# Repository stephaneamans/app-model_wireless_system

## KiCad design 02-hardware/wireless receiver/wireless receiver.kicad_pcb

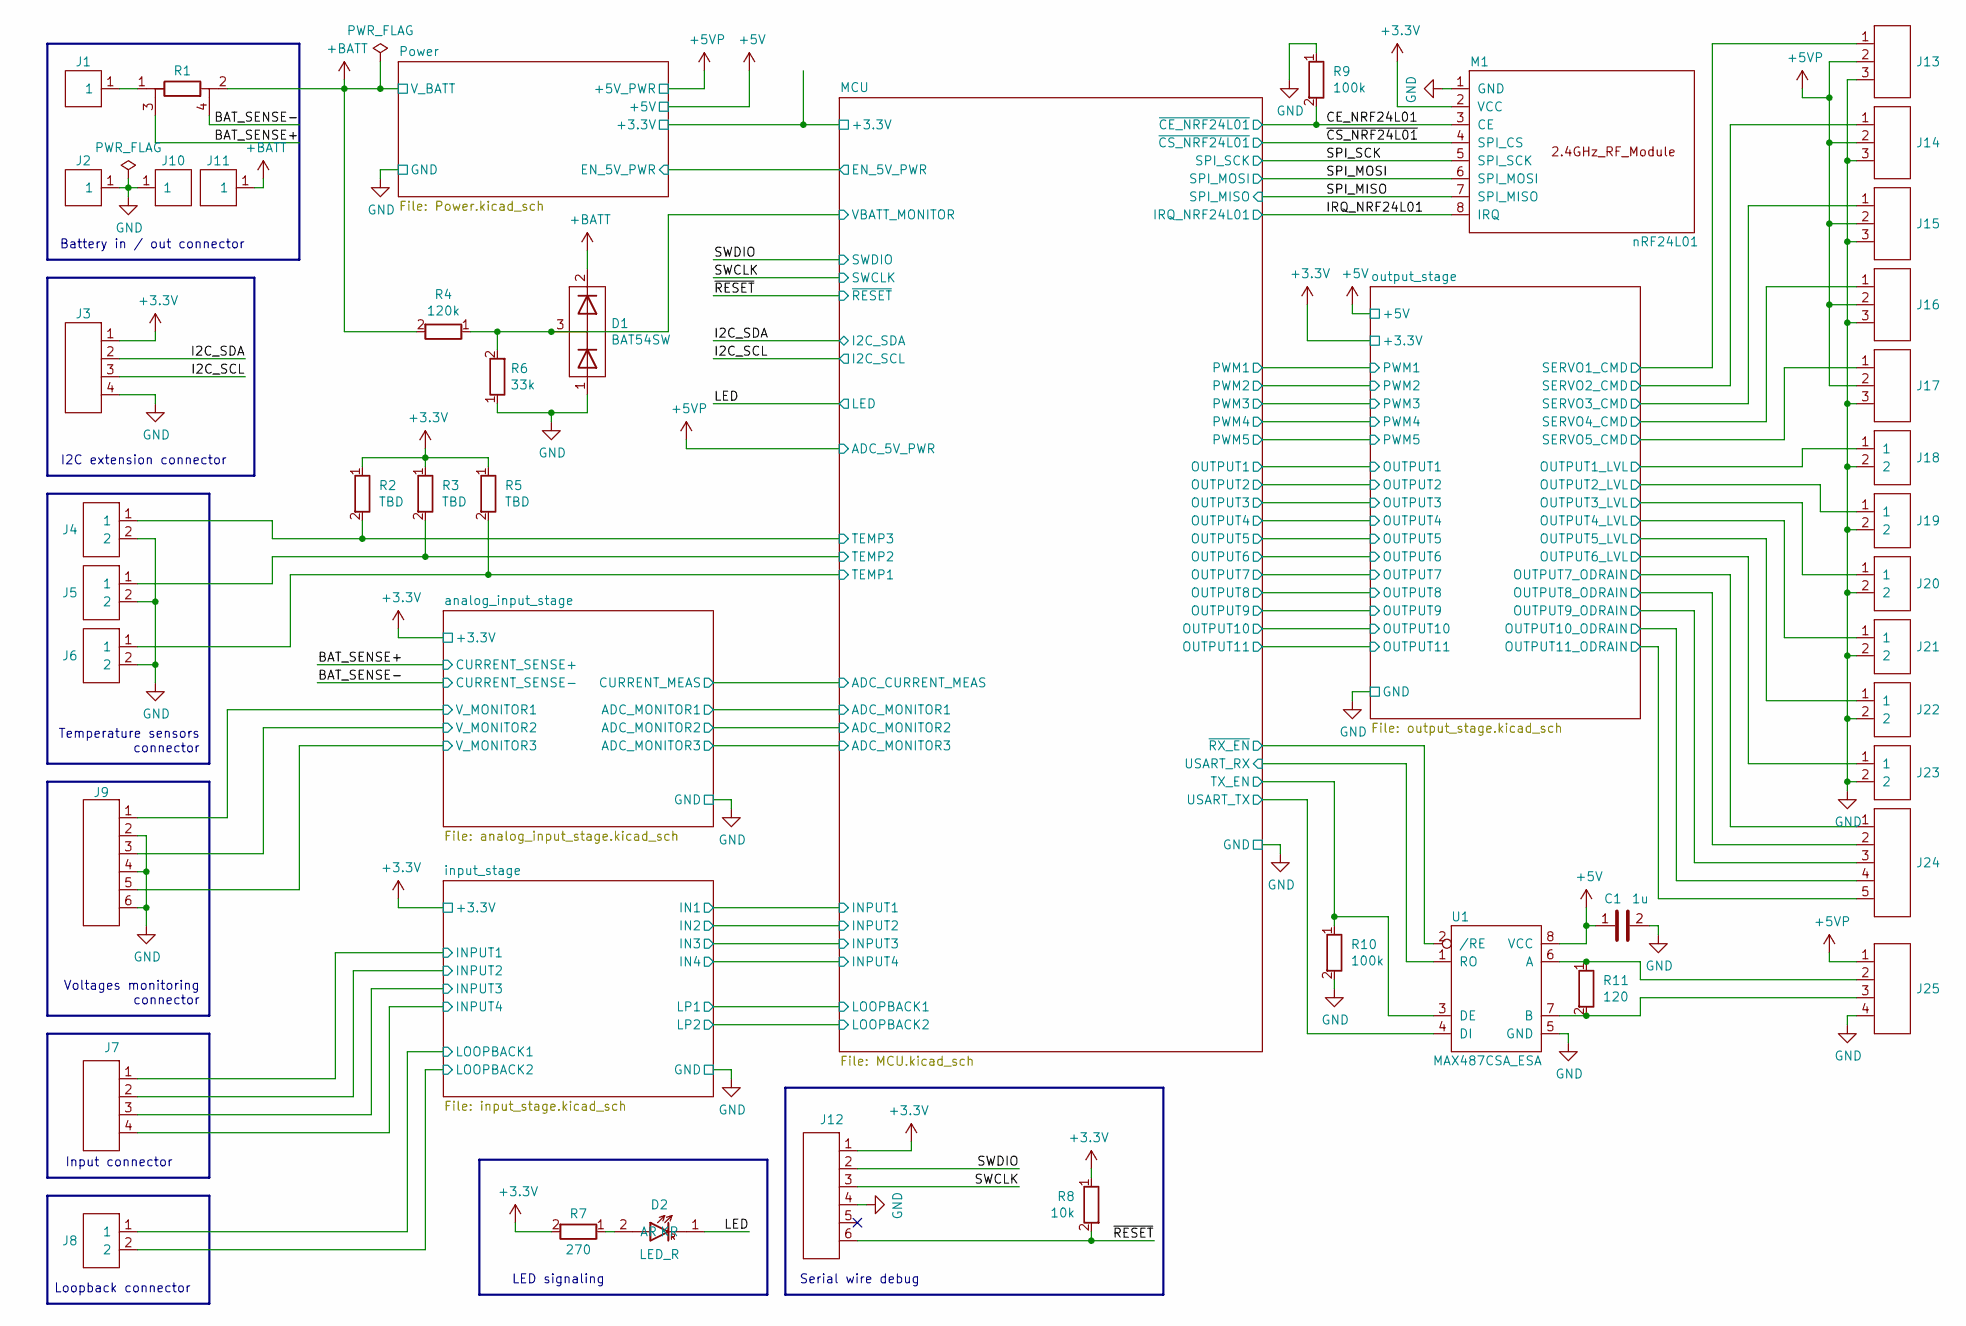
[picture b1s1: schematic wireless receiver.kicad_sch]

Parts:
C1: 1u; C_0603_1608Metric_Pad1.08x0.95mm_HandSolder
D1: BAT54SW; SOT-323
D2: LED_R; LED_0603_1608Metric
J1, J2, J10, J11: Conn_HE13_1x1_5.08V; PinHeader_1x01_P5.08mm_Vertical
J3, J7, J25: Conn_HE13_1x4_2.54V; PinHeader_1x04_P2.54mm_Vertical
J4, J5, J6, J8, J18, J19, J20, J21, J22, J23: Conn_HE13_1x2_2.54V; PinHeader_1x02_P2.54mm_Vertical
J9, J12: Conn_HE13_1x6_2.54H; PinHeader_1x06_P2.54mm_Horizontal
J13, J14, J15, J16, J17: Conn_HE13_1x3_2.54V; PinHeader_1x03_P2.54mm_Vertical
J24: Conn_HE13_1x5_2.54V; PinHeader_1x05_P2.54mm_Vertical
M1: nRF24L01; nRF24L01_Breakout
R1: R_shunt_2512; R_2512_6332Metric_shunt
R2, R3, R5: TBD; R_0603_1608Metric_Pad0.98x0.95mm_HandSolder
R4: 120k; R_0603_1608Metric_Pad0.98x0.95mm_HandSolder
R6: 33k; R_0603_1608Metric_Pad0.98x0.95mm_HandSolder
R7: 270; R_0603_1608Metric_Pad0.98x0.95mm_HandSolder
R8: 10k; R_0603_1608Metric_Pad0.98x0.95mm_HandSolder
R9, R10: 100k; R_0603_1608Metric_Pad0.98x0.95mm_HandSolder
R11: 120; R_0603_1608Metric_Pad0.98x0.95mm_HandSolder
U1: MAX487CSA_ESA; SOIC-8_3.9x4.9mm_P1.27mm

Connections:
+3.3V: J3.1, J12.1, M1.2 (VCC), R2.1, R3.1, R5.1, R7.2, R8.1; also elsewhere on the board
+5V: C1.1, U1.8 (VCC); also elsewhere on the board
+5VP: J13.2, J14.2, J15.2, J16.2, J17.2, J25.1; also elsewhere on the board
+BATT: D1.2 (K), J11.1, R1.2, R4.2; also elsewhere on the board
/BAT_SENSE+: R1.3; also elsewhere on the board
/BAT_SENSE-: R1.4; also elsewhere on the board
/CE_NRF24L01: M1.3 (CE), R9.2; also elsewhere on the board
/I2C_SCL: J3.3; also elsewhere on the board
/I2C_SDA: J3.2; also elsewhere on the board
/IRQ_NRF24L01: M1.8 (IRQ); also elsewhere on the board
/LED: D2.1 (KR); also elsewhere on the board
/MCU/TEMP1: J6.1, R5.2; also elsewhere on the board
/MCU/TEMP2: J5.1, R3.2; also elsewhere on the board
/MCU/TEMP3: J4.1, R2.2; also elsewhere on the board
/MCU/TX_EN: R10.1, U1.3 (DE); also elsewhere on the board
/MCU/USART_RX: U1.1 (RO); also elsewhere on the board
/MCU/USART_TX: U1.4 (DI); also elsewhere on the board
/MCU/VBATT_MONITOR: D1.3 (A/K), R4.1, R6.2; also elsewhere on the board
/MCU/~RX_EN: U1.2 (/RE); also elsewhere on the board
/SPI_MISO: M1.7 (SPI_MISO); also elsewhere on the board
/SPI_MOSI: M1.6 (SPI_MOSI); also elsewhere on the board
/SPI_SCK: M1.5 (SPI_SCK); also elsewhere on the board
/SWCLK: J12.3; also elsewhere on the board
/SWDIO: J12.2; also elsewhere on the board
/analog_input_stage/V_MONITOR1: J9.1; also elsewhere on the board
/analog_input_stage/V_MONITOR2: J9.3; also elsewhere on the board
/analog_input_stage/V_MONITOR3: J9.5; also elsewhere on the board
/input_stage/INPUT1: J7.1; also elsewhere on the board
/input_stage/INPUT2: J7.2; also elsewhere on the board
/input_stage/INPUT3: J7.3; also elsewhere on the board
/input_stage/INPUT4: J7.4; also elsewhere on the board
/input_stage/LOOPBACK1: J8.1; also elsewhere on the board
/input_stage/LOOPBACK2: J8.2; also elsewhere on the board
/output_stage/OUTPUT1_LVL: J18.1; also elsewhere on the board
/output_stage/OUTPUT2_LVL: J19.1; also elsewhere on the board
/output_stage/OUTPUT3_LVL: J20.1; also elsewhere on the board
/output_stage/OUTPUT4_LVL: J21.1; also elsewhere on the board
/output_stage/OUTPUT5_LVL: J22.1; also elsewhere on the board
/output_stage/OUTPUT6_LVL: J23.1; also elsewhere on the board
/output_stage/OUTPUT7_ODRAIN: J24.1; also elsewhere on the board
/output_stage/OUTPUT8_ODRAIN: J24.2; also elsewhere on the board
/output_stage/OUTPUT9_ODRAIN: J24.3; also elsewhere on the board
/output_stage/OUTPUT10_ODRAIN: J24.4; also elsewhere on the board
/output_stage/OUTPUT11_ODRAIN: J24.5; also elsewhere on the board
/output_stage/SERVO1_CMD: J13.1; also elsewhere on the board
/output_stage/SERVO2_CMD: J14.1; also elsewhere on the board
/output_stage/SERVO3_CMD: J15.1; also elsewhere on the board
/output_stage/SERVO4_CMD: J16.1; also elsewhere on the board
/output_stage/SERVO5_CMD: J17.1; also elsewhere on the board
/~CS_NRF24L01: M1.4 (SPI_CS); also elsewhere on the board
/~RESET: J12.6, R8.2; also elsewhere on the board
GND: C1.2, D1.1 (A), J2.1, J3.4, J4.2, J5.2, J6.2, J9.2, J9.4, J9.6, J10.1, J12.4, J13.3, J14.3, J15.3, J16.3, J17.3, J18.2, J19.2, J20.2, J21.2, J22.2, J23.2, J25.4, M1.1 (GND), R6.1, R9.1, R10.2, U1.5 (GND); also elsewhere on the board
unnamed: D2.2 (AR), R7.1
unnamed: J1.1, R1.1
unnamed: J25.2, R11.1, U1.6 (A)
unnamed: J25.3, R11.2, U1.7 (B)

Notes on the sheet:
Input connector
LED signaling
Battery in / out connector
I2C extension connector
Serial wire debug
Voltages monitoring connector
Temperature sensors connector
Loopback connector

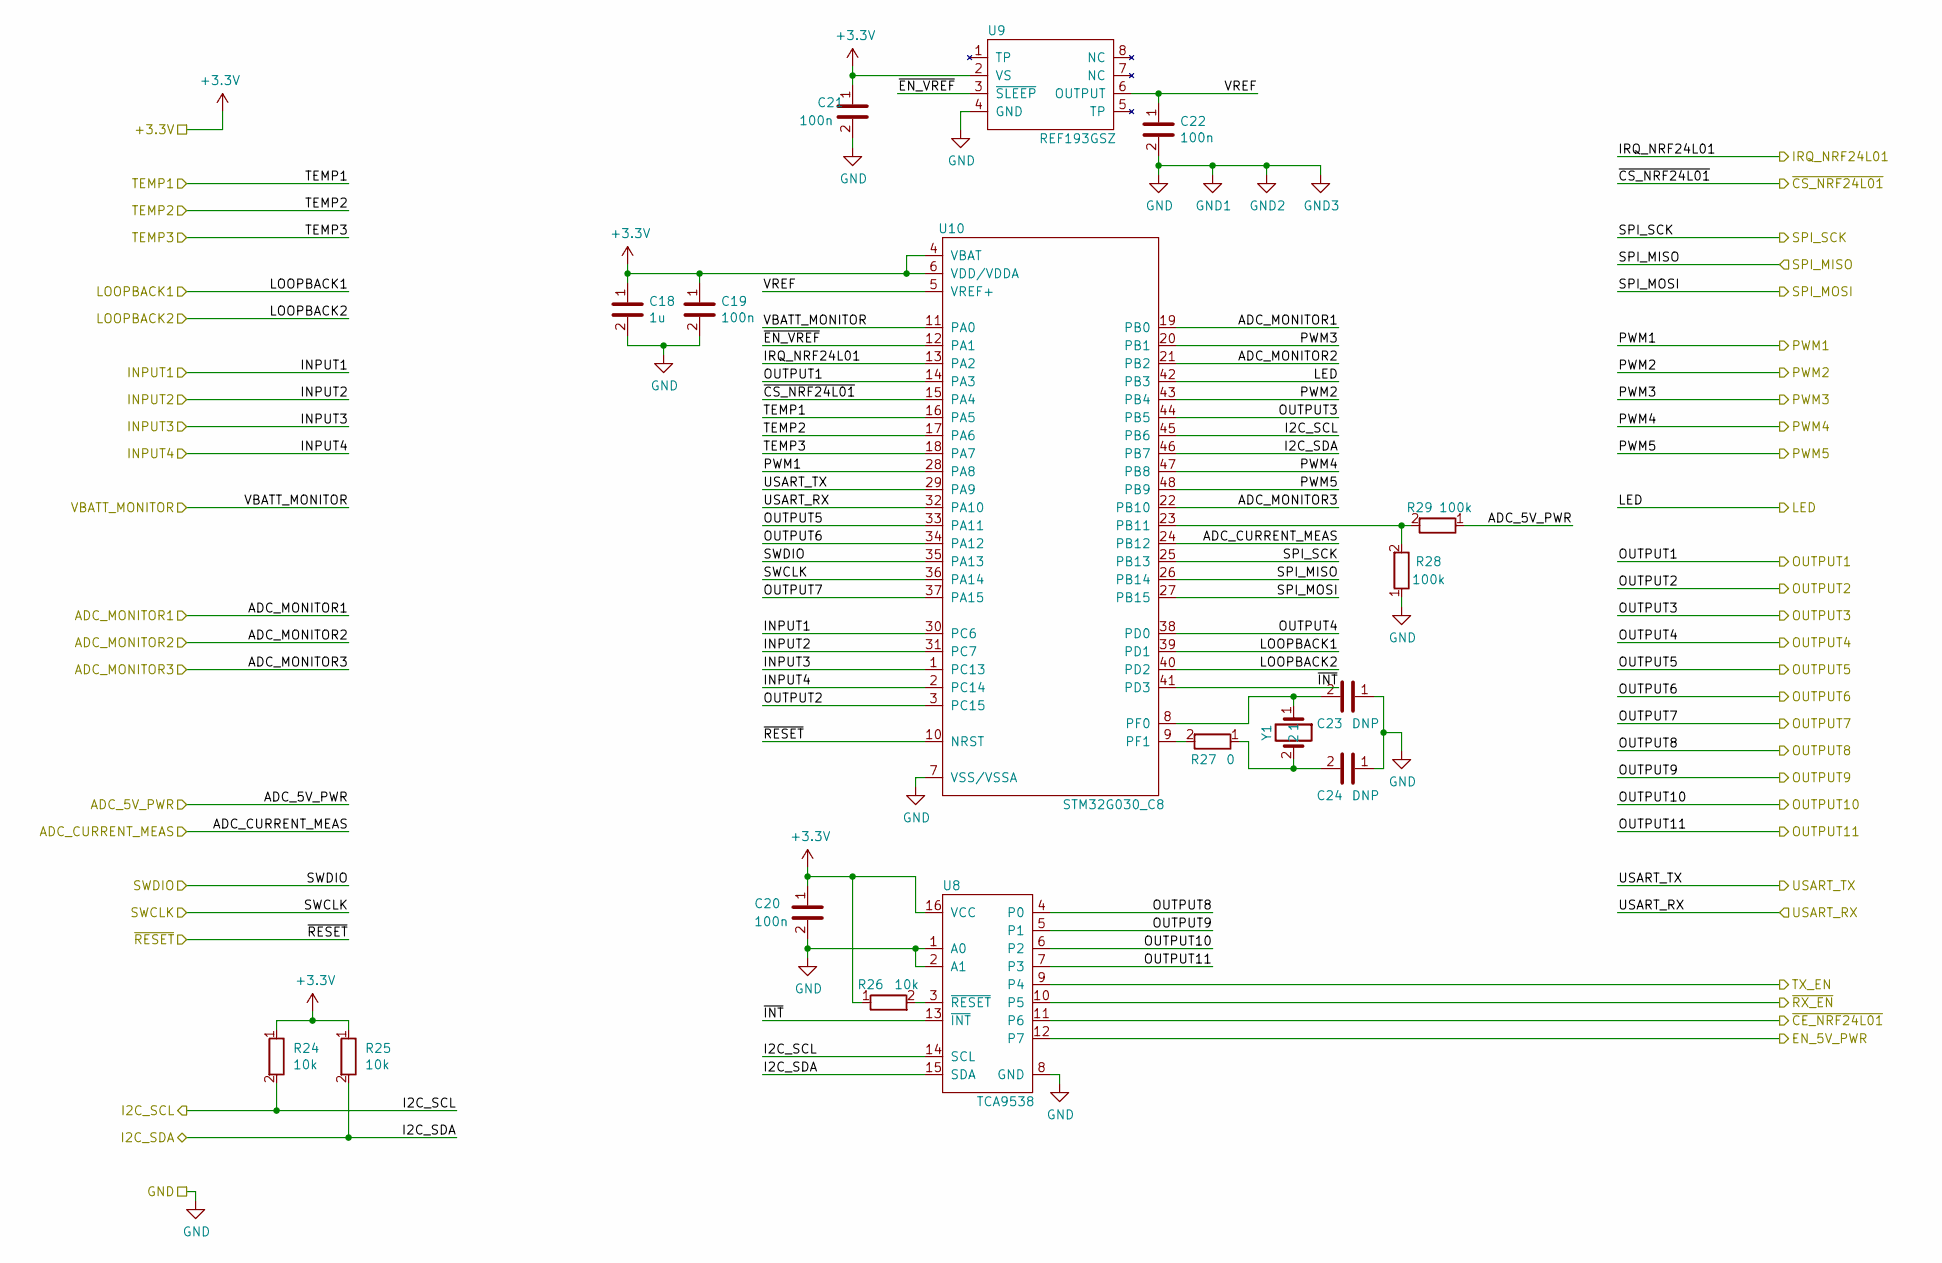
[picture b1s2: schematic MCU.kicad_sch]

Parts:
C18: 1u; C_0603_1608Metric_Pad1.08x0.95mm_HandSolder
C19, C20, C21, C22: 100n; C_0603_1608Metric_Pad1.08x0.95mm_HandSolder
C23, C24: DNP; C_0603_1608Metric_Pad1.08x0.95mm_HandSolder
R24, R25, R26: 10k; R_0603_1608Metric_Pad0.98x0.95mm_HandSolder
R27: 0; R_0603_1608Metric_Pad0.98x0.95mm_HandSolder
R28, R29: 100k; R_0603_1608Metric_Pad0.98x0.95mm_HandSolder
U8: TCA9538; SSOP-16_5.3x6.2mm_P0.65mm
U9: REF193GSZ; SOIC-8_3.9x4.9mm_P1.27mm
U10: STM32G030_C8; LQFP-48_7x7mm_P0.5mm
Y1: Crystal_HC49CMS; Crystal_SMD_HC49-SD_HandSoldering

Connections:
+3.3V: C18.1, C19.1, C20.1, C21.1, R24.1, R25.1, R26.1, U8.16 (VCC), U9.2 (VS), U10.4 (VBAT), U10.6 (VDD/VDDA); also elsewhere on the board
+5VP: R29.1; also elsewhere on the board
/CE_NRF24L01: U8.11 (P6); also elsewhere on the board
/I2C_SCL: R24.2, U8.14 (SCL), U10.45 (PB6); also elsewhere on the board
/I2C_SDA: R25.2, U8.15 (SDA), U10.46 (PB7); also elsewhere on the board
/IRQ_NRF24L01: U10.13 (PA2); also elsewhere on the board
/LED: U10.42 (PB3); also elsewhere on the board
/MCU/ADC_CURRENT_MEAS: U10.24 (PB12); also elsewhere on the board
/MCU/ADC_MONITOR1: U10.19 (PB0); also elsewhere on the board
/MCU/ADC_MONITOR2: U10.21 (PB2); also elsewhere on the board
/MCU/ADC_MONITOR3: U10.22 (PB10); also elsewhere on the board
/MCU/EN_5V_PWR: U8.12 (P7); also elsewhere on the board
/MCU/INPUT1: U10.30 (PC6); also elsewhere on the board
/MCU/INPUT2: U10.31 (PC7); also elsewhere on the board
/MCU/INPUT3: U10.1 (PC13); also elsewhere on the board
/MCU/INPUT4: U10.2 (PC14); also elsewhere on the board
/MCU/LOOPBACK1: U10.39 (PD1); also elsewhere on the board
/MCU/LOOPBACK2: U10.40 (PD2); also elsewhere on the board
/MCU/OUTPUT1: U10.14 (PA3); also elsewhere on the board
/MCU/OUTPUT2: U10.3 (PC15); also elsewhere on the board
/MCU/OUTPUT3: U10.44 (PB5); also elsewhere on the board
/MCU/OUTPUT4: U10.38 (PD0); also elsewhere on the board
/MCU/OUTPUT5: U10.33 (PA11); also elsewhere on the board
/MCU/OUTPUT6: U10.34 (PA12); also elsewhere on the board
/MCU/OUTPUT7: U10.37 (PA15); also elsewhere on the board
/MCU/OUTPUT8: U8.4 (P0); also elsewhere on the board
/MCU/OUTPUT9: U8.5 (P1); also elsewhere on the board
/MCU/OUTPUT10: U8.6 (P2); also elsewhere on the board
/MCU/OUTPUT11: U8.7 (P3); also elsewhere on the board
/MCU/PWM1: U10.28 (PA8); also elsewhere on the board
/MCU/PWM2: U10.43 (PB4); also elsewhere on the board
/MCU/PWM3: U10.20 (PB1); also elsewhere on the board
/MCU/PWM4: U10.47 (PB8); also elsewhere on the board
/MCU/PWM5: U10.48 (PB9); also elsewhere on the board
/MCU/TEMP1: U10.16 (PA5); also elsewhere on the board
/MCU/TEMP2: U10.17 (PA6); also elsewhere on the board
/MCU/TEMP3: U10.18 (PA7); also elsewhere on the board
/MCU/TX_EN: U8.9 (P4); also elsewhere on the board
/MCU/USART_RX: U10.32 (PA10); also elsewhere on the board
/MCU/USART_TX: U10.29 (PA9); also elsewhere on the board
/MCU/VBATT_MONITOR: U10.11 (PA0); also elsewhere on the board
/MCU/VREF: C22.1, U9.6 (OUTPUT), U10.5 (VREF+)
/MCU/~EN_VREF: U9.3 (~SLEEP), U10.12 (PA1)
/MCU/~INT: U8.13 (~INT), U10.41 (PD3)
/MCU/~RX_EN: U8.10 (P5); also elsewhere on the board
/SPI_MISO: U10.26 (PB14); also elsewhere on the board
/SPI_MOSI: U10.27 (PB15); also elsewhere on the board
/SPI_SCK: U10.25 (PB13); also elsewhere on the board
/SWCLK: U10.36 (PA14); also elsewhere on the board
/SWDIO: U10.35 (PA13); also elsewhere on the board
/~CS_NRF24L01: U10.15 (PA4); also elsewhere on the board
/~RESET: U10.10 (NRST); also elsewhere on the board
GND: C18.2, C19.2, C20.2, C21.2, C22.2, C23.1, C24.1, R28.1, U8.1 (A0), U8.2 (A1), U8.8 (GND), U9.4 (GND), U10.7 (VSS/VSSA); also elsewhere on the board
unnamed: C23.2, U10.8 (PF0), Y1.1
unnamed: C24.2, R27.1, Y1.2
unnamed: R26.2, U8.3 (~RESET)
unnamed: R27.2, U10.9 (PF1)
unnamed: R28.2, R29.2, U10.23 (PB11)

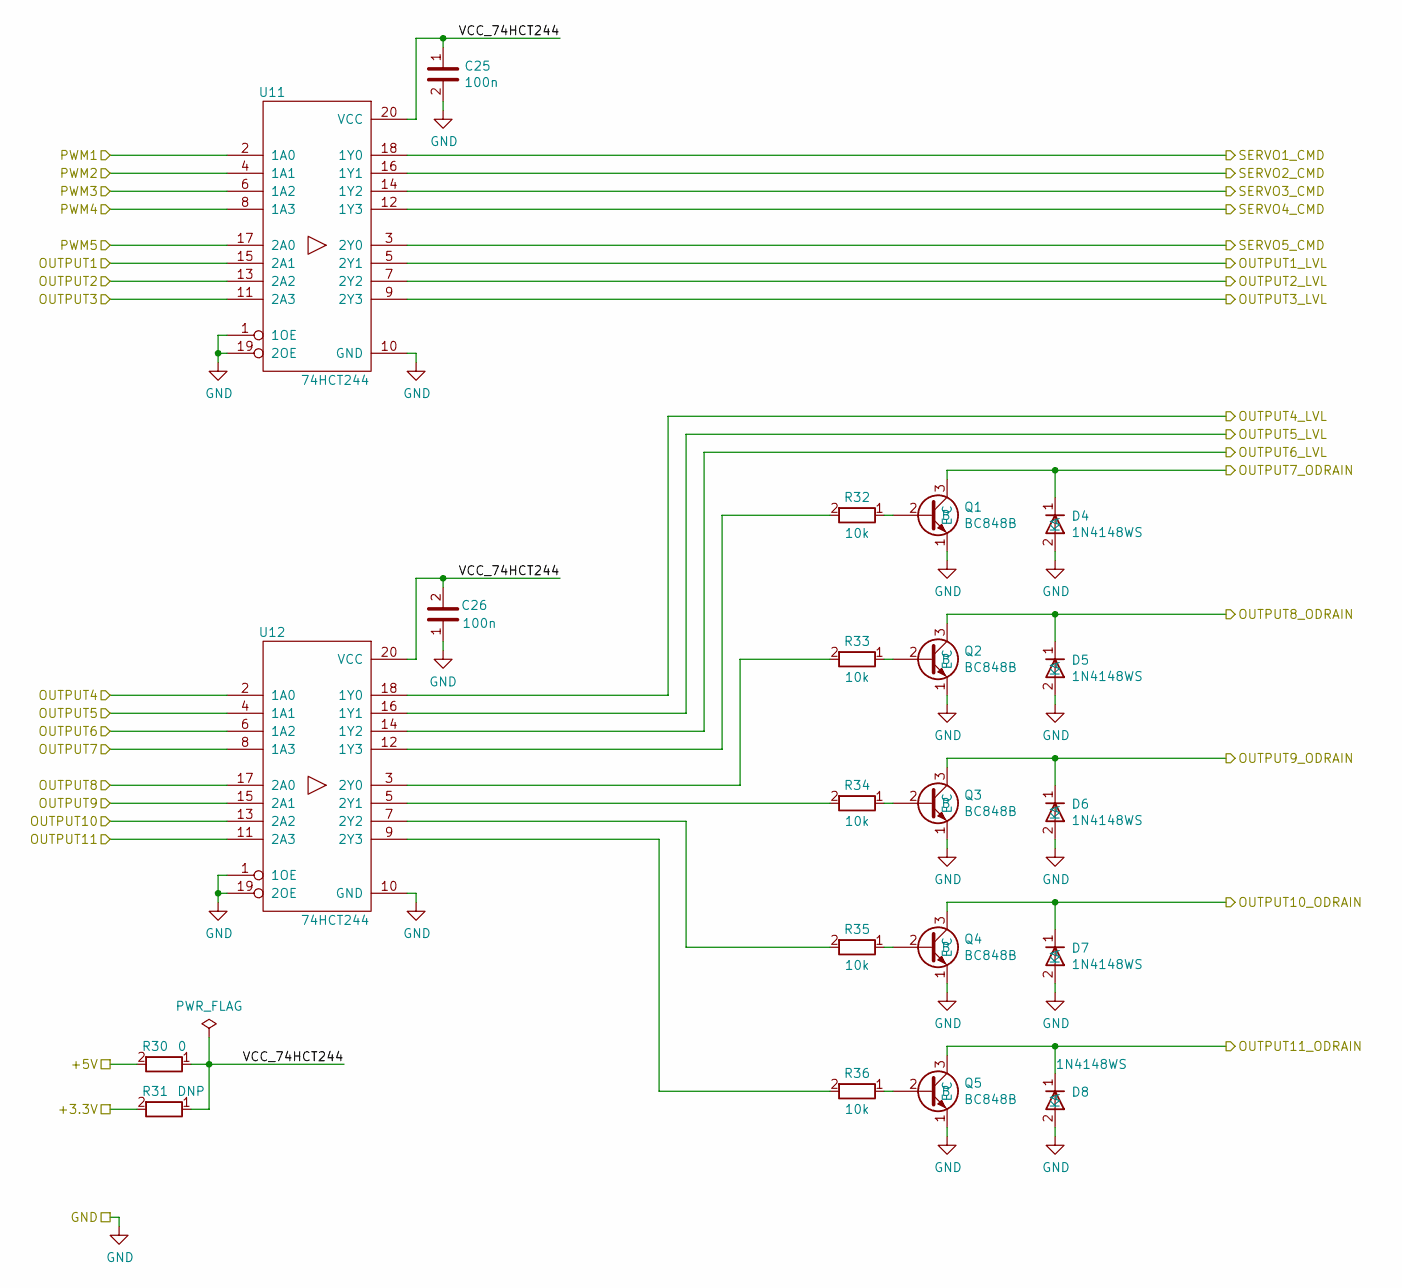
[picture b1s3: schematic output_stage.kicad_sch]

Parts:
C25, C26: 100n; C_0603_1608Metric_Pad1.08x0.95mm_HandSolder
D4, D5, D6, D7, D8: 1N4148WS; D_SOD-323_HandSoldering
Q1, Q2, Q3, Q4, Q5: BC848B; SOT-23
R30: 0; R_0603_1608Metric_Pad0.98x0.95mm_HandSolder
R31: DNP; R_0603_1608Metric_Pad0.98x0.95mm_HandSolder
R32, R33, R34, R35, R36: 10k; R_0603_1608Metric_Pad0.98x0.95mm_HandSolder
U11, U12: 74HCT244; SOIC-20W_7.5x12.8mm_P1.27mm

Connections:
+3.3V: R31.2; also elsewhere on the board
+5V: R30.2; also elsewhere on the board
/MCU/OUTPUT1: U11.15 (2A1); also elsewhere on the board
/MCU/OUTPUT2: U11.13 (2A2); also elsewhere on the board
/MCU/OUTPUT3: U11.11 (2A3); also elsewhere on the board
/MCU/OUTPUT4: U12.2 (1A0); also elsewhere on the board
/MCU/OUTPUT5: U12.4 (1A1); also elsewhere on the board
/MCU/OUTPUT6: U12.6 (1A2); also elsewhere on the board
/MCU/OUTPUT7: U12.8 (1A3); also elsewhere on the board
/MCU/OUTPUT8: U12.17 (2A0); also elsewhere on the board
/MCU/OUTPUT9: U12.15 (2A1); also elsewhere on the board
/MCU/OUTPUT10: U12.13 (2A2); also elsewhere on the board
/MCU/OUTPUT11: U12.11 (2A3); also elsewhere on the board
/MCU/PWM1: U11.2 (1A0); also elsewhere on the board
/MCU/PWM2: U11.4 (1A1); also elsewhere on the board
/MCU/PWM3: U11.6 (1A2); also elsewhere on the board
/MCU/PWM4: U11.8 (1A3); also elsewhere on the board
/MCU/PWM5: U11.17 (2A0); also elsewhere on the board
/output_stage/OUTPUT1_LVL: U11.5 (2Y1); also elsewhere on the board
/output_stage/OUTPUT2_LVL: U11.7 (2Y2); also elsewhere on the board
/output_stage/OUTPUT3_LVL: U11.9 (2Y3); also elsewhere on the board
/output_stage/OUTPUT4_LVL: U12.18 (1Y0); also elsewhere on the board
/output_stage/OUTPUT5_LVL: U12.16 (1Y1); also elsewhere on the board
/output_stage/OUTPUT6_LVL: U12.14 (1Y2); also elsewhere on the board
/output_stage/OUTPUT7_ODRAIN: D4.1 (K), Q1.3 (C); also elsewhere on the board
/output_stage/OUTPUT8_ODRAIN: D5.1 (K), Q2.3 (C); also elsewhere on the board
/output_stage/OUTPUT9_ODRAIN: D6.1 (K), Q3.3 (C); also elsewhere on the board
/output_stage/OUTPUT10_ODRAIN: D7.1 (K), Q4.3 (C); also elsewhere on the board
/output_stage/OUTPUT11_ODRAIN: D8.1 (K), Q5.3 (C); also elsewhere on the board
/output_stage/SERVO1_CMD: U11.18 (1Y0); also elsewhere on the board
/output_stage/SERVO2_CMD: U11.16 (1Y1); also elsewhere on the board
/output_stage/SERVO3_CMD: U11.14 (1Y2); also elsewhere on the board
/output_stage/SERVO4_CMD: U11.12 (1Y3); also elsewhere on the board
/output_stage/SERVO5_CMD: U11.3 (2Y0); also elsewhere on the board
/output_stage/VCC_74HCT244: C25.1, C26.2, R30.1, R31.1, U11.20 (VCC), U12.20 (VCC)
GND: C25.2, C26.1, D4.2 (A), D5.2 (A), D6.2 (A), D7.2 (A), D8.2 (A), Q1.1 (E), Q2.1 (E), Q3.1 (E), Q4.1 (E), Q5.1 (E), U11.1 (1OE), U11.10 (GND), U11.19 (2OE), U12.1 (1OE), U12.10 (GND), U12.19 (2OE); also elsewhere on the board
unnamed: Q1.2 (B), R32.1
unnamed: Q2.2 (B), R33.1
unnamed: Q3.2 (B), R34.1
unnamed: Q4.2 (B), R35.1
unnamed: Q5.2 (B), R36.1
unnamed: R32.2, U12.12 (1Y3)
unnamed: R33.2, U12.3 (2Y0)
unnamed: R34.2, U12.5 (2Y1)
unnamed: R35.2, U12.7 (2Y2)
unnamed: R36.2, U12.9 (2Y3)

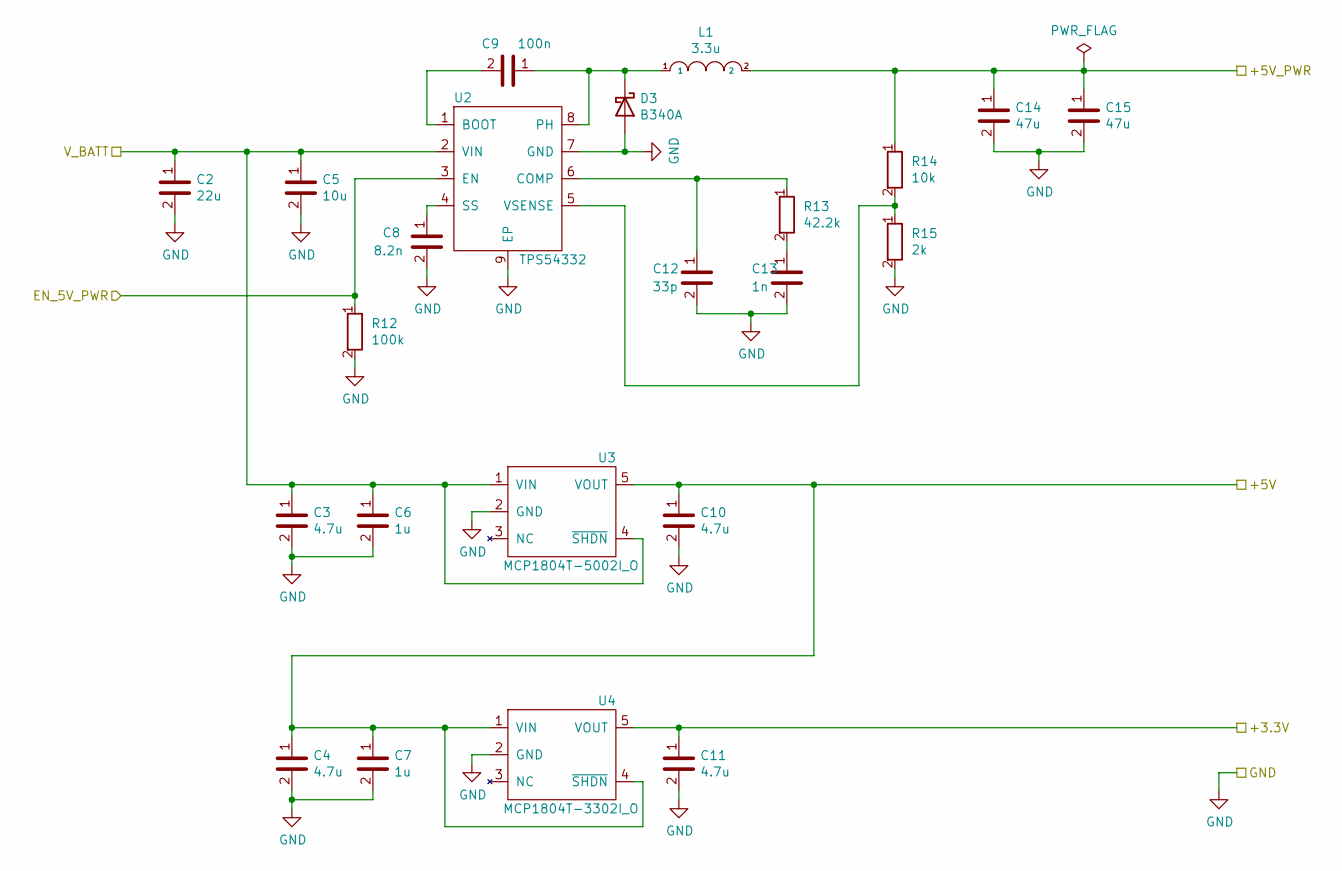
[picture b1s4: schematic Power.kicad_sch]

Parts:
C2: 22u; C_1210_3225Metric_Pad1.33x2.70mm_HandSolder
C3, C4: 4.7u; C_0805_2012Metric_Pad1.18x1.45mm_HandSolder
C5: 10u; C_1206_3216Metric_Pad1.33x1.80mm_HandSolder
C6, C7: 1u; C_0603_1608Metric_Pad1.08x0.95mm_HandSolder
C8: 8.2n; C_0603_1608Metric_Pad1.08x0.95mm_HandSolder
C9: 100n; C_0603_1608Metric_Pad1.08x0.95mm_HandSolder
C10, C11: 4.7u; C_0603_1608Metric_Pad1.08x0.95mm_HandSolder
C12: 33p; C_0603_1608Metric_Pad1.08x0.95mm_HandSolder
C13: 1n; C_0603_1608Metric_Pad1.08x0.95mm_HandSolder
C14, C15: 47u; C_1210_3225Metric_Pad1.33x2.70mm_HandSolder
D3: B340A; D_SMA_Handsoldering
L1: 3.3u; L_Vishay_IHLP-2525
R12: 100k; R_0603_1608Metric_Pad0.98x0.95mm_HandSolder
R13: 42.2k; R_0603_1608Metric_Pad0.98x0.95mm_HandSolder
R14: 10k; R_0603_1608Metric_Pad0.98x0.95mm_HandSolder
R15: 2k; R_0603_1608Metric_Pad0.98x0.95mm_HandSolder
U2: TPS54332; SOIC-8-1EP_3.9x4.9mm_P1.27mm_EP2.29x3mm
U3: MCP1804T-5002I_O; SOT-23-5
U4: MCP1804T-3302I_O; SOT-23-5

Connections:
+3.3V: C11.1, U4.5 (VOUT); also elsewhere on the board
+5V: C4.1, C7.1, C10.1, U3.5 (VOUT), U4.1 (VIN), U4.4 (~SHDN); also elsewhere on the board
+5VP: C14.1, C15.1, L1.2, R14.1; also elsewhere on the board
+BATT: C2.1, C3.1, C5.1, C6.1, U2.2 (VIN), U3.1 (VIN), U3.4 (~SHDN); also elsewhere on the board
/MCU/EN_5V_PWR: R12.1, U2.3 (EN); also elsewhere on the board
GND: C2.2, C3.2, C4.2, C5.2, C6.2, C7.2, C8.2, C10.2, C11.2, C12.2, C13.2, C14.2, C15.2, D3.2 (A), R12.2, R15.2, U2.7 (GND), U2.9 (EP), U3.2 (GND), U4.2 (GND); also elsewhere on the board
unnamed: C8.1, U2.4 (SS)
unnamed: C9.1, D3.1 (K), L1.1, U2.8 (PH)
unnamed: C9.2, U2.1 (BOOT)
unnamed: C12.1, R13.1, U2.6 (COMP)
unnamed: C13.1, R13.2
unnamed: R14.2, R15.1, U2.5 (VSENSE)

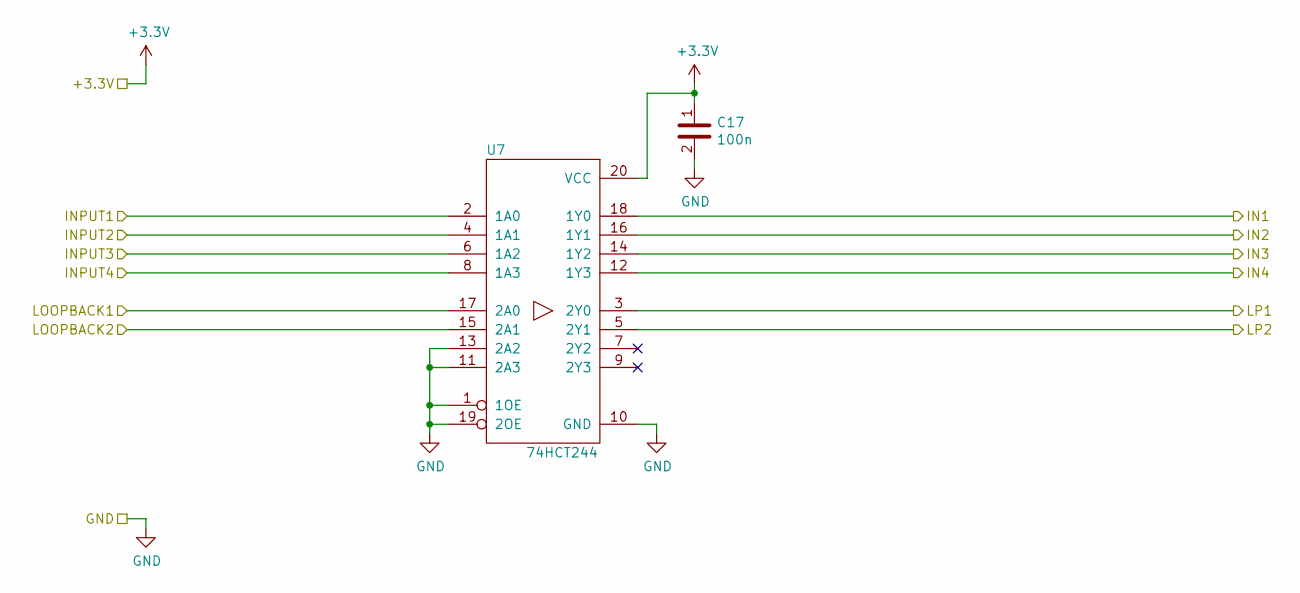
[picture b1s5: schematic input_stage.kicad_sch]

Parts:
C17: 100n; C_0603_1608Metric_Pad1.08x0.95mm_HandSolder
U7: 74HCT244; SOIC-20W_7.5x12.8mm_P1.27mm

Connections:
+3.3V: C17.1, U7.20 (VCC); also elsewhere on the board
/MCU/INPUT1: U7.18 (1Y0); also elsewhere on the board
/MCU/INPUT2: U7.16 (1Y1); also elsewhere on the board
/MCU/INPUT3: U7.14 (1Y2); also elsewhere on the board
/MCU/INPUT4: U7.12 (1Y3); also elsewhere on the board
/MCU/LOOPBACK1: U7.3 (2Y0); also elsewhere on the board
/MCU/LOOPBACK2: U7.5 (2Y1); also elsewhere on the board
/input_stage/INPUT1: U7.2 (1A0); also elsewhere on the board
/input_stage/INPUT2: U7.4 (1A1); also elsewhere on the board
/input_stage/INPUT3: U7.6 (1A2); also elsewhere on the board
/input_stage/INPUT4: U7.8 (1A3); also elsewhere on the board
/input_stage/LOOPBACK1: U7.17 (2A0); also elsewhere on the board
/input_stage/LOOPBACK2: U7.15 (2A1); also elsewhere on the board
GND: C17.2, U7.1 (1OE), U7.10 (GND), U7.11 (2A3), U7.13 (2A2), U7.19 (2OE); also elsewhere on the board

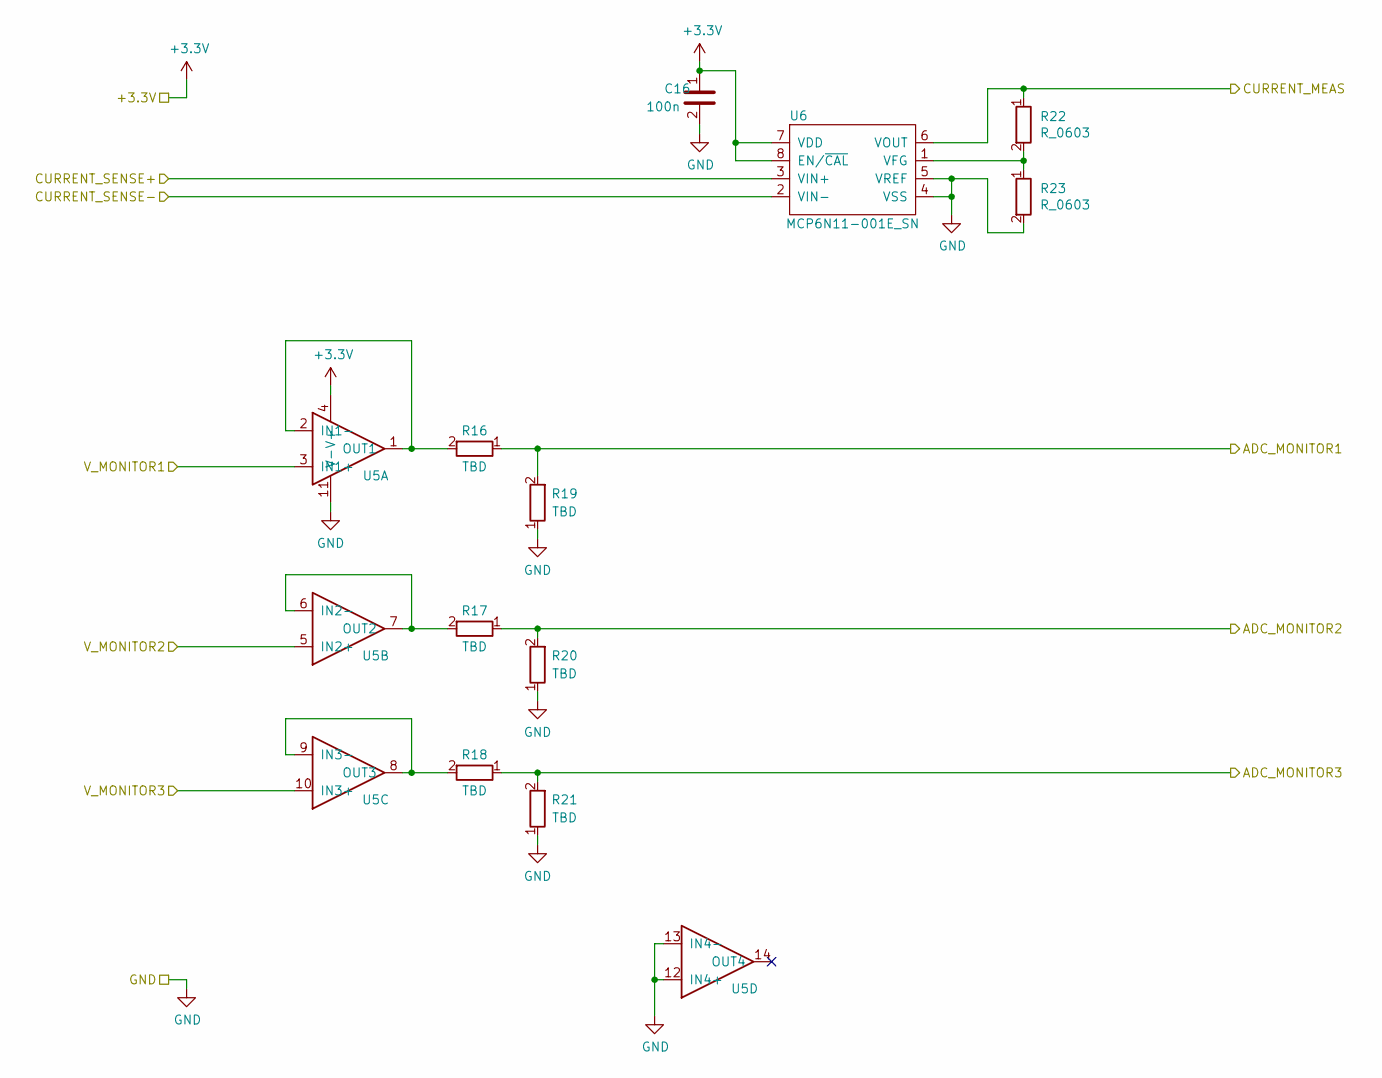
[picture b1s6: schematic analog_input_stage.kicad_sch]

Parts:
C16: 100n; C_0603_1608Metric_Pad1.08x0.95mm_HandSolder
R16, R17, R18, R19, R20, R21: TBD; R_0603_1608Metric_Pad0.98x0.95mm_HandSolder
R22, R23: R_0603; R_0603_1608Metric_Pad0.98x0.95mm_HandSolder
U5: LMV824AIYDT; SO-14_3.9x8.65mm_P1.27mm
U6: MCP6N11-001E_SN; SOIC-8_3.9x4.9mm_P1.27mm

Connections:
+3.3V: C16.1, U5.4 (V+), U6.7 (VDD), U6.8 (EN/~CAL); also elsewhere on the board
/BAT_SENSE+: U6.3 (VIN+); also elsewhere on the board
/BAT_SENSE-: U6.2 (VIN-); also elsewhere on the board
/MCU/ADC_CURRENT_MEAS: R22.1, U6.6 (VOUT); also elsewhere on the board
/MCU/ADC_MONITOR1: R16.1, R19.2; also elsewhere on the board
/MCU/ADC_MONITOR2: R17.1, R20.2; also elsewhere on the board
/MCU/ADC_MONITOR3: R18.1, R21.2; also elsewhere on the board
/analog_input_stage/V_MONITOR1: U5.3 (IN1+); also elsewhere on the board
/analog_input_stage/V_MONITOR2: U5.5 (IN2+); also elsewhere on the board
/analog_input_stage/V_MONITOR3: U5.10 (IN3+); also elsewhere on the board
GND: C16.2, R19.1, R20.1, R21.1, R23.2, U5.11 (V-), U5.12 (IN4+), U5.13 (IN4-), U6.4 (VSS), U6.5 (VREF); also elsewhere on the board
unnamed: R16.2, U5.1 (OUT1), U5.2 (IN1-)
unnamed: R17.2, U5.6 (IN2-), U5.7 (OUT2)
unnamed: R18.2, U5.8 (OUT3), U5.9 (IN3-)
unnamed: R22.2, R23.1, U6.1 (VFG)

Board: 2 copper layers, 115 parts (0 on the bottom side), 112 nets, no tracks yet.

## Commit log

2021-03-31 modeling transmiter v1.0
2021-03-31 Project architecture
2021-04-02 Transmiter project creation
2021-04-02 Receiver project creation
2022-08-11 Receiver schematic ended and migration to KiCAD 6.0
2022-08-11 PCB base
